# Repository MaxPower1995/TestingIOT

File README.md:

# Modulo Zeus

# Versiones 
| Version | Fecha | Notas de la versión |
|---------|-------|-------------|
| 1.1 | 06/09/2024  | Versión de Alberto, agregue unos defines|
| 1.2 | 06/09/2024  | Arreglo el README.md |
| 1.3 | 10/10/2024 | Se cambia totalmente la logica |
| 1.4 | 26/11/2024 | Nivel de agua con flotadores |
| 1.5 | 27/11/2024 | Se agrega el aprpadeo del led |
| 1.6 | 27/11/2024 | Mayor robutez a la conexion WiFi |
| 1.7 | 29/11/2024 | Se arregla problema de prioridad en tareas |
| 1.8 | 29/11/2024 | Se agrega la lectura de los DS18B20 |
| 1.9 | 04/12/2024 | Se arregla nomenclatura de los sensores |
| 2.0 | 26/02/2025 | Server HTTP funcionando |

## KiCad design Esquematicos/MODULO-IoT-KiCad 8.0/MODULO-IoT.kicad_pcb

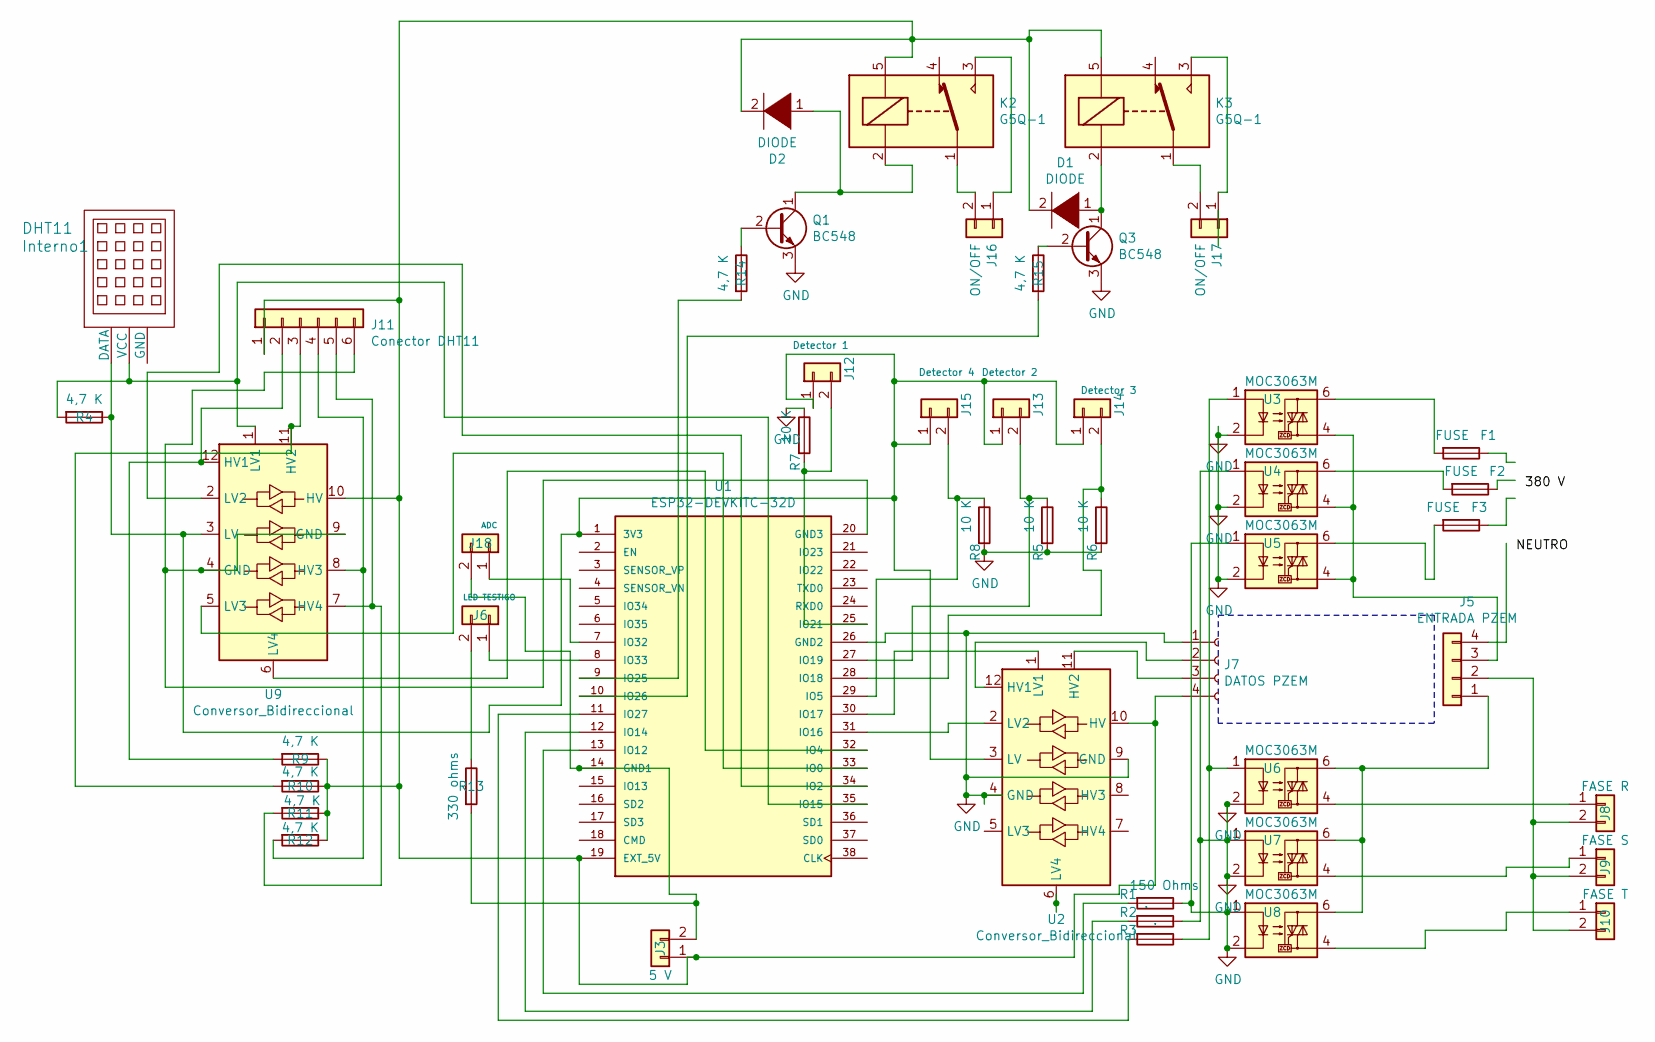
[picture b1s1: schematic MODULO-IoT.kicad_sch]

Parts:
D1, D2: DIODE; D_A-405_P2.54mm_Vertical_AnodeUp
F1, F2, F3: FUSE; Fuse_Bourns_MF-RG300
Interno1: DHT11; Aosong_DHT11_5.5x12.0_P2.54mm
J3: 5 V; PinHeader_1x02_P2.54mm_Vertical
J5: ENTRADA PZEM; TerminalBlock_Phoenix_MKDS-1,5-4-5.08_1x04_P5.08mm_Horizont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
J6: LED TESTIGO; PinHeader_1x02_P2.54mm_Vertical
J7: DATOS PZEM; PinHeader_1x04_P2.54mm_Vertical
J8: FASE R; TerminalBlock_Phoenix_MKDS-1,5-2-5.08_1x02_P5.08mm_Horizont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
J9: FASE S; TerminalBlock_Phoenix_MKDS-1,5-2-5.08_1x02_P5.08mm_Horizont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
J10: FASE T; TerminalBlock_Phoenix_MKDS-1,5-2-5.08_1x02_P5.08mm_Horizont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
J11: Conector DHT11; TerminalBlock_Phoenix_MKDS-1,5-6_1x06_P5.00mm_Horizontal
J12: Detector 1; TerminalBlock_Phoenix_MKDS-1,5-2-5.08_1x02_P5.08mm_Horizont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
J13: Detector 2; TerminalBlock_Phoenix_MKDS-1,5-2-5.08_1x02_P5.08mm_Horizont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
J14: Detector 3; TerminalBlock_Phoenix_MKDS-1,5-2-5.08_1x02_P5.08mm_Horizont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
J15: Detector 4; TerminalBlock_Phoenix_MKDS-1,5-2-5.08_1x02_P5.08mm_Horizont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
J16, J17: ON/OFF; TerminalBlock_Phoenix_MKDS-1,5-2-5.08_1x02_P5.08mm_Horizont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
J18: ADC; PinHeader_1x02_P2.54mm_Vertical
K2, K3: G5Q-1; Relay_SPDT_Omron-G5LE-1
Q1, Q3: BC548; TO-126-3_Vertical
R1: 150 Ohms; R_Axial_DIN0207_L6.3mm_D2.5mm_P10.16mm_Horizontal
R2, R3: .; R_Axial_DIN0207_L6.3mm_D2.5mm_P10.16mm_Horizontal
R4, R9, R10, R11, R12, R14, R15: 4,7 K; R_Axial_DIN0309_L9.0mm_D3.2mm_P5.08mm_Vertical
R5, R6, R7, R8: 10 K; R_Axial_DIN0207_L6.3mm_D2.5mm_P10.16mm_Horizontal
R13: 330 ohms; R_Axial_DIN0309_L9.0mm_D3.2mm_P5.08mm_Vertical
U1: ESP32-DEVKITC-32D; MODULE_ESP32-DEVKITC-32D
U2, U9: Conversor_Bidireccional; DIP-12_W10.16mm_LongPads
U3, U4, U5, U6, U7, U8: MOC3063M; DIP-6_W7.62mm

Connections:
GND: J7.1, Q1.3 (E), Q3.3 (E), R1.1, R2.1, R5.2, R6.2, R7.1, R8.2, U1.26 (GND2), U2.4 (GND), U2.9 (GND), U3.2, U4.1, U4.2, U5.1, U5.2, U6.2, U7.1, U7.2, U8.1, U8.2
unnamed: D1.2 (A), D2.2 (A), J3.1, J7.4, J11.1, K2.5, K3.5, R9.1, R10.1, R11.1, R12.1, U1.19 (EXT_5V), U2.10 (HV), U9.10 (HV)
unnamed: D1.1 (K), K3.2, Q3.1 (C)
unnamed: D2.1 (K), K2.2, Q1.1 (C)
unnamed: F1.2, U3.6
unnamed: F2.2, U4.6
unnamed: F3.2, U5.6
unnamed: Interno1.1 (DATA), J12.1, J13.1, J14.1, J15.1, R4.1, U1.1 (3V3), U2.3 (LV), U9.3 (LV)
unnamed: Interno1.2 (VCC), R4.2, U1.35 (IO15), U9.1 (LV1)
unnamed: J5.1, U6.6, U7.6, U8.6
unnamed: J5.3, U3.4, U4.4, U5.4
unnamed: J6.1, U1.8 (IO33)
unnamed: J6.2, R13.1
unnamed: J7.2, U2.12 (HV1)
unnamed: J7.3, U2.11 (HV2)
unnamed: J8.1, U6.4
unnamed: J9.1, U7.4
unnamed: J10.1, U8.4
unnamed: J5.2, J8.2, J9.2, J10.2
unnamed: J11.2, R9.2, U9.12 (HV1)
unnamed: J11.3, R10.2, U9.11 (HV2)
unnamed: J11.4, R12.2, U9.8 (HV3)
unnamed: J11.5, R11.2, U9.7 (HV4)
unnamed: J11.6, U1.20 (GND3), U9.4 (GND), U9.9 (GND)
unnamed: J12.2, R7.2, U1.25 (IO21)
unnamed: J13.2, R5.1, U1.27 (IO19)
unnamed: J14.2, R6.1, U1.28 (IO18)
unnamed: J15.2, R8.1, U1.29 (IO5)
unnamed: J16.1, K2.3
unnamed: J16.2, K2.1
unnamed: J17.1, K3.3
unnamed: J17.2, K3.1
unnamed: J18.1, U1.7 (IO32)
unnamed: J3.2, J18.2, R13.2, U1.14 (GND1)
unnamed: Q1.2 (B), R14.1
unnamed: Q3.2 (B), R15.1
unnamed: R3.1, U3.1, U6.1
unnamed: U1.33 (IO0), U9.5 (LV3)
unnamed: U1.34 (IO2), U9.2 (LV2)
unnamed: U1.32 (IO4), U9.6 (LV4)
unnamed: R1.2, U1.13 (IO12)
unnamed: R2.2, U1.12 (IO14)
unnamed: U1.31 (IO16), U2.2 (LV2)
unnamed: U1.30 (IO17), U2.1 (LV1)
unnamed: R14.2, U1.9 (IO25)
unnamed: R15.2, U1.10 (IO26)
unnamed: R3.2, U1.11 (IO27)

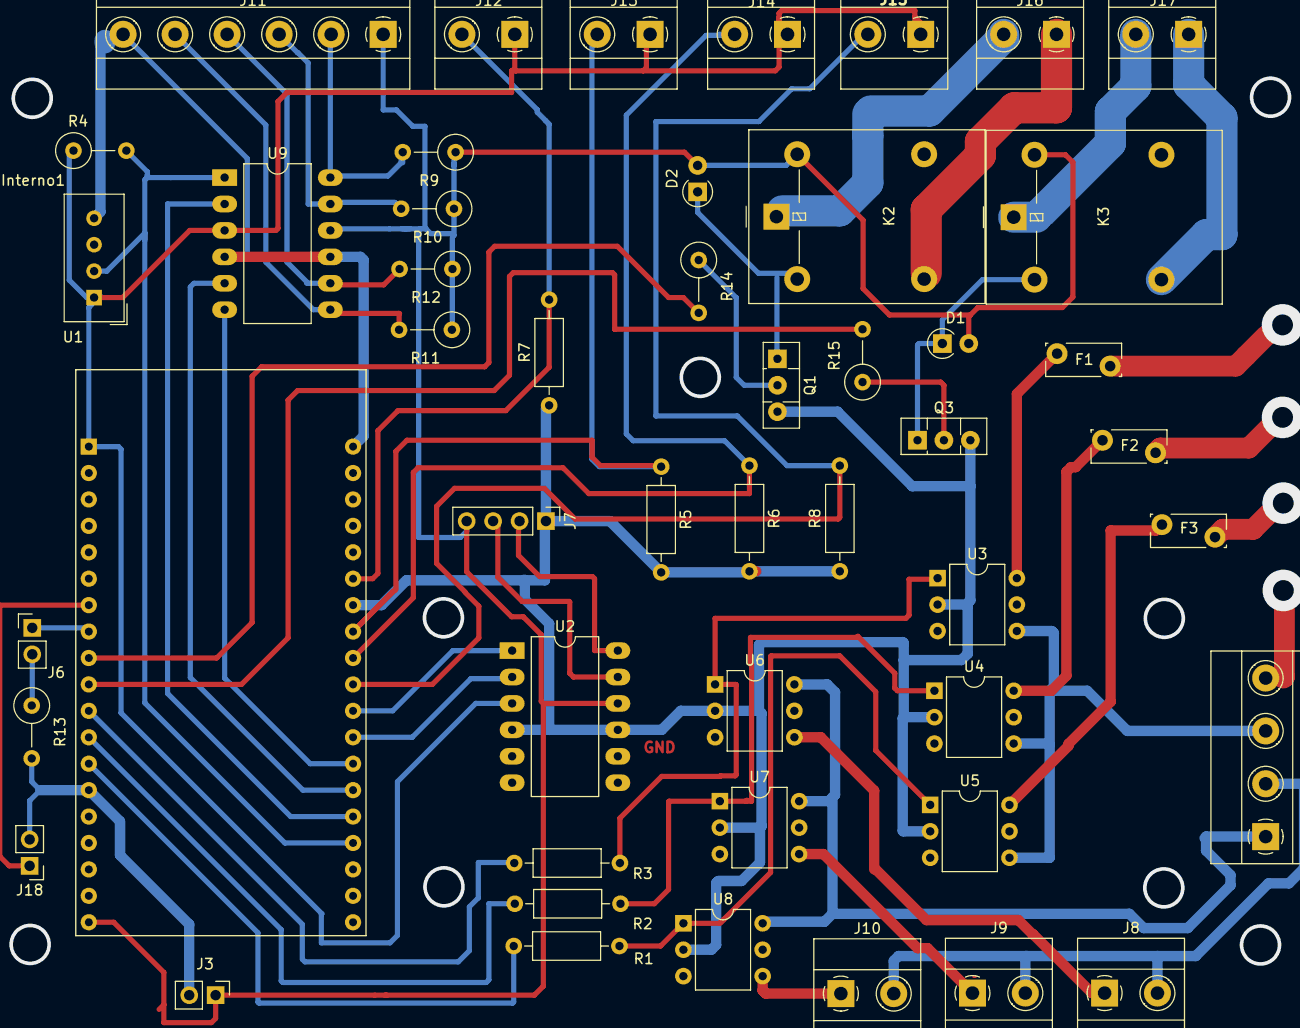
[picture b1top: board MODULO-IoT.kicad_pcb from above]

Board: 2 copper layers, 49 parts (0 on the bottom side), 47 nets.

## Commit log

2025-02-19 Primer commit
2025-02-26 | 2.0 | 26/02/2025 | Server HTTP funcionando |
2025-03-07 | 2.2 | 07/03/2025 | Se agregan automatizacions |
